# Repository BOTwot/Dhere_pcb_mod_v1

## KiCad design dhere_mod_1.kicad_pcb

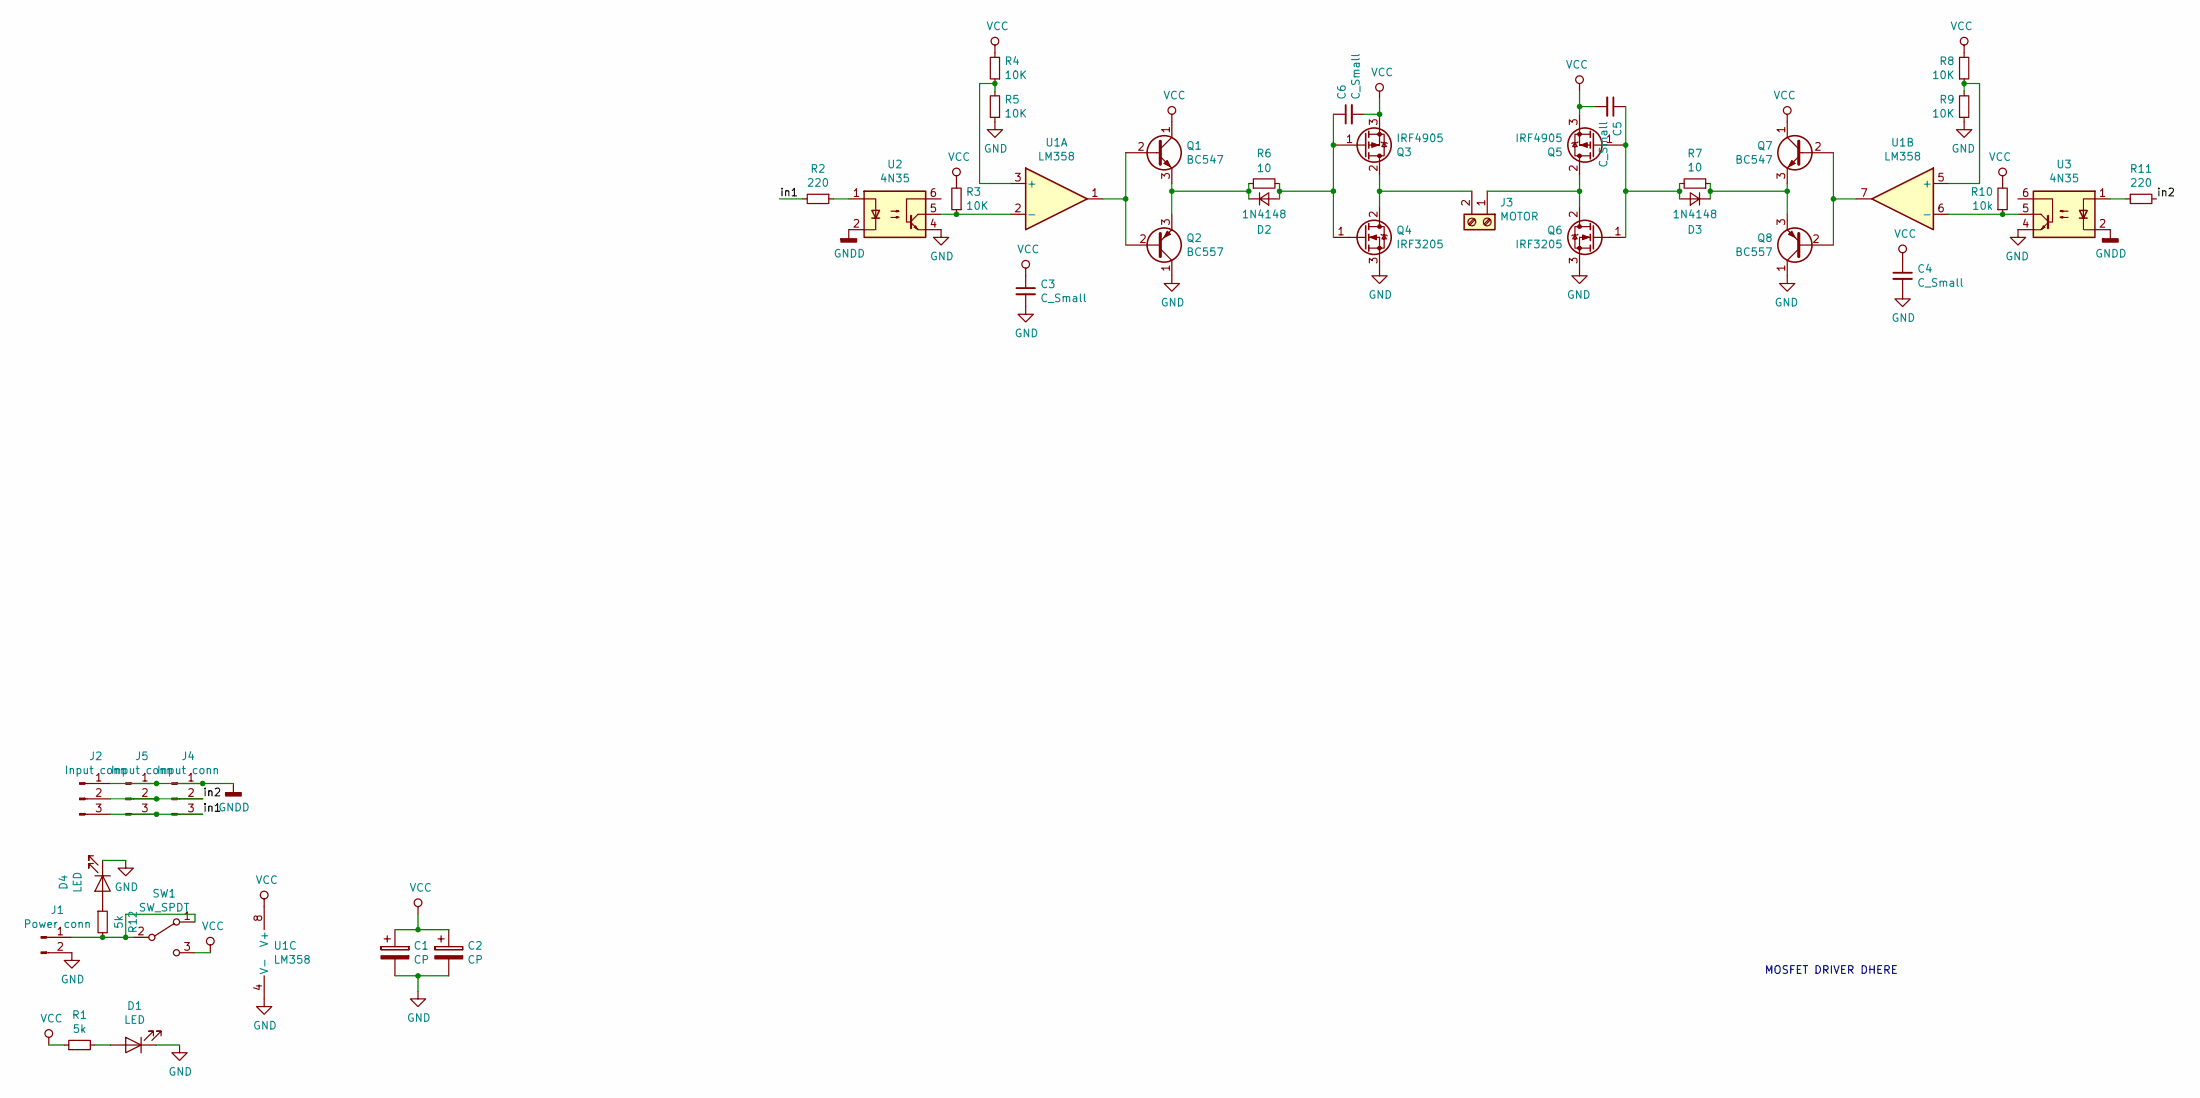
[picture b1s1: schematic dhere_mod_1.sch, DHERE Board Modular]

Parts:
C1, C2: CP; CP_Radial_D10.0mm_P2.50mm_P5.00mm
C3, C4, C5, C6: C_Small; C_0805_2012Metric
D1, D4: LED; LED_D5.0mm_FlatTop
D2, D3: 1N4148; D_A-405_P7.62mm_Horizontal
J1: Power conn; TerminalBlock_Altech_AK300-2_P5.00mm
J2: Input conn; JST_EH_S03B-EH_1x03_P2.50mm_Horizontal
J3: MOTOR; TerminalBlock_Altech_AK300-2_P5.00mm
J4, J5: Input conn; PinHeader_1x03_P2.54mm_Vertical
Q1, Q7: BC547; TO-92_Wide
Q2, Q8: BC557; TO-92_Wide
Q3, Q5: IRF4905; TO-220-3_Vertical
Q4, Q6: IRF3205; TO-220-3_Vertical
R1, R12: 5k; R_0805_2012Metric_Pad1.15x1.40mm_HandSolder
R2, R11: 220; R_Axial_DIN0207_L6.3mm_D2.5mm_P7.62mm_Horizontal
R3, R4, R5, R8, R9: 10K; R_Axial_DIN0207_L6.3mm_D2.5mm_P7.62mm_Horizontal
R6, R7: 10; R_Axial_DIN0207_L6.3mm_D2.5mm_P7.62mm_Horizontal
R10: 10k; R_Axial_DIN0207_L6.3mm_D2.5mm_P7.62mm_Horizontal
SW1: SW_SPDT; SW_CuK_OS102011MA1QN1_SPDT_Angled
U1: LM358; DIP-8_W7.62mm_Socket_LongPads
U2, U3: 4N35; DIP-6_W7.62mm

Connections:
/in1: J2.3, J4.3, J5.3, R2.2
/in2: J2.2, J4.2, J5.2, R11.2
GND: C1.2, C2.2, C3.2, C4.2, D1.1 (K), D4.1 (K), J1.2, Q2.1 (C), Q4.3 (S), Q6.3 (S), Q8.1 (C), R5.1, R9.1, U1.4 (V-), U2.4, U3.4
GNDD: J2.1, J4.1, J5.1, U2.2, U3.2
unnamed: C5.1, D3.2 (A), Q5.1 (G), Q6.1 (G), R7.2
unnamed: C6.1, D2.2 (A), Q3.1 (G), Q4.1 (G), R6.2
unnamed: D1.2 (A), R1.2
unnamed: D2.1 (K), Q1.3 (E), Q2.3 (E), R6.1
unnamed: D3.1 (K), Q7.3 (E), Q8.3 (E), R7.1
unnamed: D4.2 (A), R12.1
unnamed: J1.1, R12.2, SW1.1 (A), SW1.2 (B)
unnamed: J3.1, Q5.2 (D), Q6.2 (D)
unnamed: J3.2, Q3.2 (D), Q4.2 (D)
unnamed: Q1.2 (B), Q2.2 (B), U1.1
unnamed: Q7.2 (B), Q8.2 (B), U1.7
unnamed: R2.1, U2.1
unnamed: R3.1, U1.2 (-), U2.5
unnamed: R4.1, R5.2, U1.3 (+)
unnamed: R8.1, R9.2, U1.5 (+)
unnamed: R10.1, U1.6 (-), U3.5
unnamed: R11.1, U3.1
VCC: C1.1, C2.1, C3.1, C4.1, C5.2, C6.2, Q1.1 (C), Q3.3 (S), Q5.3 (S), Q7.1 (C), R1.1, R3.2, R4.2, R8.2, R10.2, SW1.3 (C), U1.8 (V+)

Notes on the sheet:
MOSFET DRIVER DHERE

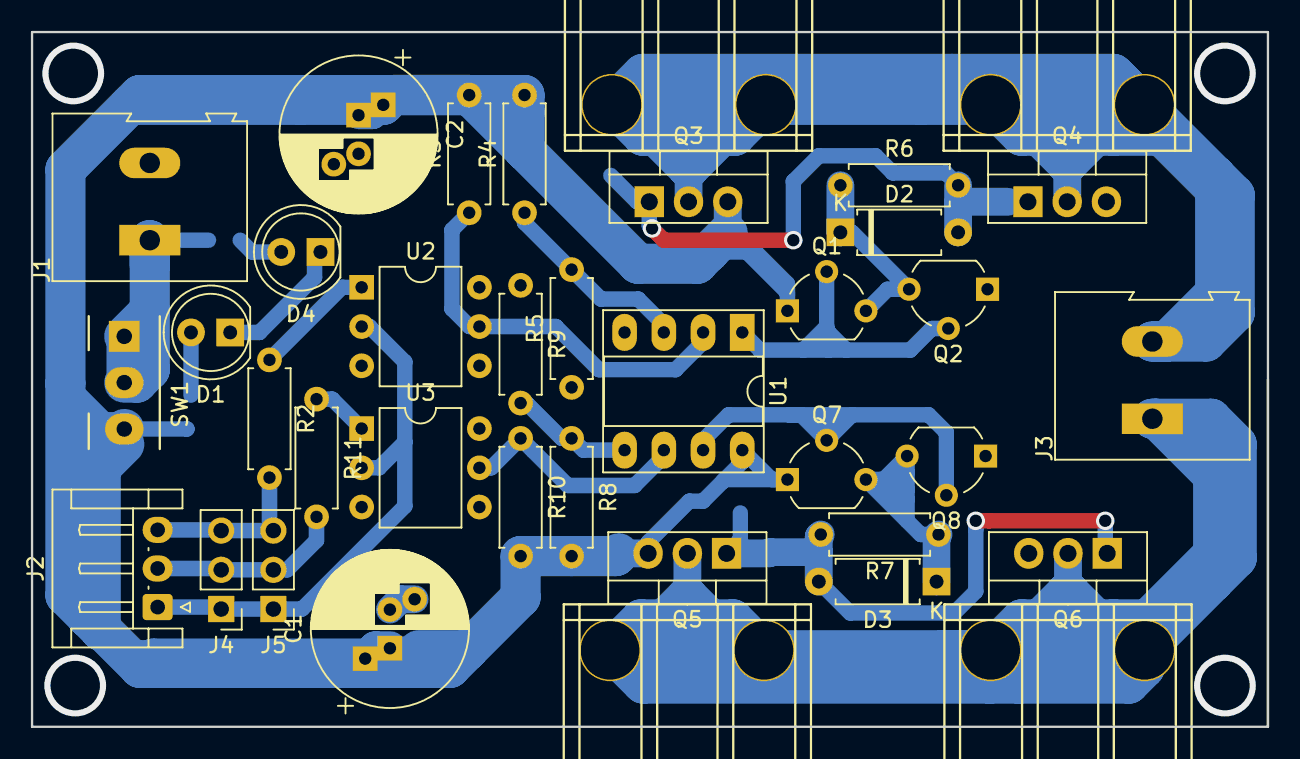
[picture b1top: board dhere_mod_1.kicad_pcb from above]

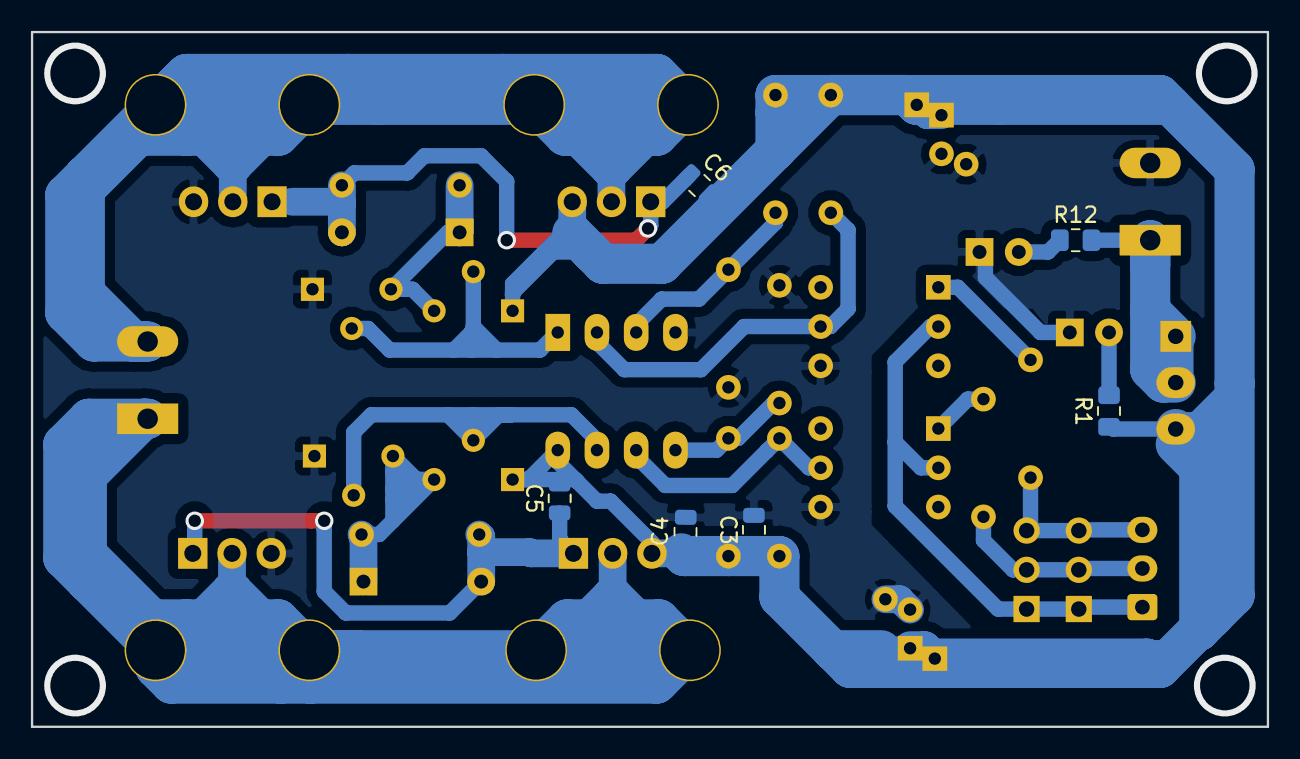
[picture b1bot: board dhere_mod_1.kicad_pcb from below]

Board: 2 copper layers, 80.0 x 45.0 mm, 39 parts (6 on the bottom side), 22 nets.

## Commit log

2019-01-16 first commit
    v1.0
2019-01-21 #2 fixed
